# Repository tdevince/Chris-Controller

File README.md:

# Chris-Controller

[](https://private-user-images.githubusercontent.com/97317875/435509045-00b4797d-aa02-43c4-9b9c-edfc26d2068e.mp4?jwt=eyJhbGciOiJIUzI1NiIsInR5cCI6IkpXVCJ9.eyJpc3MiOiJnaXRodWIuY29tIiwiYXVkIjoicmF3LmdpdGh1YnVzZXJjb250ZW50LmNvbSIsImtleSI6ImtleTUiLCJleHAiOjE3NDUxOTc4OTksIm5iZiI6MTc0NTE5NzU5OSwicGF0aCI6Ii85NzMxNzg3NS80MzU1MDkwNDUtMDBiNDc5N2QtYWEwMi00M2M0LTliOWMtZWRmYzI2ZDIwNjhlLm1wND9YLUFtei1BbGdvcml0aG09QVdTNC1ITUFDLVNIQTI1NiZYLUFtei1DcmVkZW50aWFsPUFLSUFWQ09EWUxTQTUzUFFLNFpBJTJGMjAyNTA0MjElMkZ1cy1lYXN0LTElMkZzMyUyRmF3czRfcmVxdWVzdCZYLUFtei1EYXRlPTIwMjUwNDIxVDAxMDYzOVomWC1BbXotRXhwaXJlcz0zMDAmWC1BbXotU2lnbmF0dXJlPWJmYWJlMGNhM2JmNDQzZDk5YWMxNTI0YjNhZTNlNTE5ZTFhZDBlNDViOGY3ZTc2ZDY3YzNkNTc0ZjY5ZTM0MTQmWC1BbXotU2lnbmVkSGVhZGVycz1ob3N0In0.5TFY-foABcXsPSkUT4TwTE6B_hcxhnk4HnvymQrl-RE)

This project is dedicated to my sister who is forced to live with a stationary oxygen concentrator 
in her house. The unit is extremely loud and not placed in a part of the house she wants to sleep 
or be in.  However, to change the oxygen flowrate, it is necessary for someone to do it at the machine.
For someone who is not mobile, this is a dificult task.  Further complicated by the fact that
in order to get up, she must first increase her oxygen flowrate.  Not possible without a caretaker
to go to the unit and manually change it.  

While some oxygen concentrators are available with remote control flow systems, they are not
FDA approved (as of this writing), as such medical supply companies do not provide these
units.

Her options are to increase the flow at the concentrator and use a second flowmeter at her location
that moves with her.  This creates a few problems, first the backpressure for the remote flowmeter
does not allow humidification at the concentrator to work properly.  Thus she is left with dry oxygen
which results in discomfort and nose bleeds.  Second, the backpressure can cause the concetrator
to alarm repeately.  Finally, this requires more hoses at her end of the system, which tangle and 
get caught when she tries to go to her walker or wheel chair.

The following paper by Duke University (https://pmc.ncbi.nlm.nih.gov/articles/PMC10122499/) provides
the basis for which this project is undertaken.  The project recommends that the controller at the 
stationary concentrator communicate via Bluetooth to a iPhone.  This requires an app on the iPhone to
controll the unit at the concentrator.  Since I'm not that well versed in creating applications for
the Apple Store, I instead created a remote control unit (based upon the ESP32-S2 chip, using the
ESP-NOW protocol).  This system uses the 2.4GHz WiFi frequency, but does not require connection
to a local WiFi network.

Since the paper that describes the hardware is a non-commercial license (CC BY-NC 3.0), the hardware
portion of this project is non-commercial. However, the software code developed for this project
is licensed under GNU General Pulbic License

## Repository Files:

* Files necessary for 3D printing are in the folder "3D Print Files".
* The Fusion360 files used to create these files are in the folder titled "Fusion360"
* An instruction manual that describes the operation and use of the system is included as a *.pdf file in the "Instruciton Manual" folder.  
* The circuit was designed using KiCad 9.0.  The schematic as well as the PCB files are in the folder "KiCad 9.0 fiies".  This folder also has the gerber files, position files and BOM files necessary for ordering the PCB's from JLCPCB.com.
* Two other repositories are used for the code used to program the controller and the remote.  The links to these repositories are in the folders "Controller" and "Remote".

## Building the Controller:

To build the Chris Controller, you will need to make the controller as well as the remote control.  The Controller consists of 3 3D printed gears, a mounting plate for the stepper motor and potentiometer and a base and cover.  The Fusion 360 files used to create the files for printing are included.  The parts were output to *stl files that were imported into PrusaSlicer.  The 3D input and output files are included in the Controller Directory.  PETG was used to print all parts. The potentiometer mounting plate requires supports on the dished part that holds the potentiometer.  The Cover has supports on the portion of the opening that accepts the 12V plug.  No other parts required supports for printing.
The stepper motor used is the 28BYJ-48 stepper motor.  This motor is found in 12V and 5V versions.  This project used the 12V version.  The potentiometer uses is the Bourns 3590-2-103L 10k ohm multiturn potentiometer.  The output jack supplied with the stepper motor is the JST 5 pin XH series connector.  The mating male connector is used on the PCB.  The potentiometer is connected to the PCB using the 2 pin JST connectors (XH series as well).  
The controller for the stepper is the ULN2003A Darlington array DIP.  Rather than use an SMT part, the DIP package was used since this is a common failure point of stepper motor systems.  Thus, using a 16pin socket on the PCB, the ULN2003A is easily replaceable.
The PCB uses an ESP32-S2-Solo-2 module for a microcontroller.  This module has the WiFi antenna included.  The code for the controller and remote uses the ESP-NOW protocol for communication.  This eliminates the need for a WiFi connection but provides superior range over a Bluetooth connection.  

The schematic and gerber files to order the PCB are provided in the KiCad directory.  The BOM used to order the PCB’s do not include the ESP32 module or any through hole parts (sockets, etc.) since these are easily added.  The ESP32 module is relatively inexpensive, but when supplied as a separate module, and not part of development kit, it must first be programmed prior to soldering to the PCB.  There is no way to update the firmware of the ESP32 once installed, other than Over-The -Air updates.  Therefore, the first loading of the firmware requires a wired connection to a PC.  Using a development board with flexipins allows for easy programming of the ESP32 module before installing.  If such a board is not available (I made my own for such purposes), the schematic and PCB can be redesigned to use a ESP32-S2-DevkitC-1.  This will increase the footprint of the PCB, but can be made functional.
The power supply used is a standard 12VDC adapter.  The stepper and ULN2003A take 12V inputs, the ESP32 is supplied with 3.3V from a buck switching regulator.  A switching regulator was chosen for its efficiency.  If a linear regulator is used, accommodation for heat dissipation must be considered since dropping from 12V to 3.3V will involve significant heat on linear regulators.

## Building the Remote:

The remote 3d files print a total of 7 items.  These are:
	Remote Cover
	Remote Base
	Up Button
	Down Button
	Battery Box
	Battery Box Cover

The Remote Cover and the Battery Box print as two items each if you want to print text(on the cover) and battery icons (on the battery box).  The text and icons are two different parts in the Fusion360 files.

To print different colors on the same layer in Prusaslicer, first go to “General” settings and change the number of extruders to 2.  Then on the Custom Code, enter “M600” for tool change.  This will cause the printer to pause and prompt to load a new color.  This method works well when only one or two layers need a different color inserted (such as text or battery icons).  When using this method, it is best if the text/icon part is part #2.  This way the rest of the layer is printed first, and success rate is higher in getting the text to look good without lifting or other print errors.

The *.gcode files are set up to print the multicolor as described above.  The cover is designed to have a 1mm thick acrylic sheet as a display window to protect the OLED screen.  The window cover should be cut and fit to the space in the cover before gluing.  Use a 5 minute epoxy rather than a CynoAcrylic (CA, Superglue, etc.) type of glue.  The CA glues will tend to fog the acrylic sheet.

The battery box uses a total of 8 keystone style 5209 terminal clips.  The clips are inserted into the box, and the tabs then bent outward 90 degrees.  The tabs then may be soldered to provide the 4 cells in series (i.e. positive to negative with the first and last tabs being the +6V and -0V tabs).

The positive tab is then routed to the slide switch (the cover is designed to use the CW Industries model G-107-SI-0005 slide switch.  The output of the slide switch, with the negative terminal of the battery box are then connected to the PCB using a JST XH series two pin connector.

Once the battery box is soldered, it may then be glued into the cover.  There are indexing tabs designed into the battery cover for the battery box.  

The two buttons (Up and Down) are also printed in PETG, I used red to offset it from the urban grey I used for the remainder of the remote.  These buttons merely fit inside the cover and are held into position by the PCB and push buttons.  The push buttons used are similar to https://www.amazon.com/Tactile-Switch-Momentary-Arduino-6x6x5mm/dp/B06XRH6GNX

Only two buttons are exposed by to the push buttons that are printed (the up and down buttons).  The calibration button is accessible using a paper clip through the small hole in the upper left of the remote cover.  The fourth button of the PCB is for OTA updates and is not accessible with the cover in place.

The remote uses a 1.3” OLED monochrome I2C display.  Note the order of the 4 contacts on the PCB to ensure that the one you are using will work, if not a redesign of the PCB may be necessary so that SDL, SCL, VCC and GND align.  The OLED uses the SH1106 chip, thus the library for the remote codes is built around this display.

Similar to the controller, the remote uses an ESP32-S2-Solo-2 bare module (https://www.digikey.com/en/products/detail/espressif-systems/ESP32-S2-SOLO-2-N4/16591892?gclid=1df37c397d151f5e88d9143c09d1c049&gclsrc=3p.ds&&utm_adgroup=General&utm_source=bing&utm_medium=cpc&utm_campaign=Dynamic%20Search_EN_RLSA_Cart&utm_term=digikey&utm_content=General&utm_id=bi_cmp-384476623_adg-1302921504343591_ad-81432677981980_dat-2333232393680003:loc-190_dev-c_ext-_prd-&msclkid=1df37c397d151f5e88d9143c09d1c049) .  

The module will need to be programmed before soldering to the PCB, so that OTA updates are possible.  The advantage of using the bare module rather than development board is that it drastically reduces the footprint on the PCB (thus a smaller remote) as well as reducing the vampire load when the module is put to sleep.  Most development boards use a linear voltage regulator, which will consume much more battery power than the switching regulator used in this design.

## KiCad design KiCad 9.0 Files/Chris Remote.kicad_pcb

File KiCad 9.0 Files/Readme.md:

This folder contains the KiCad files for the schematic and PCB layout
in the formate required by JLCPCB.com.  Also included is the BOM and
position file that JLCPCB requires for assembly.  The BOM and postion
file do not include information the push buttons, connectors or
ESP32-S2-Solo-2 module since these are manually soldered after
receipt of the manufactured PCB's.

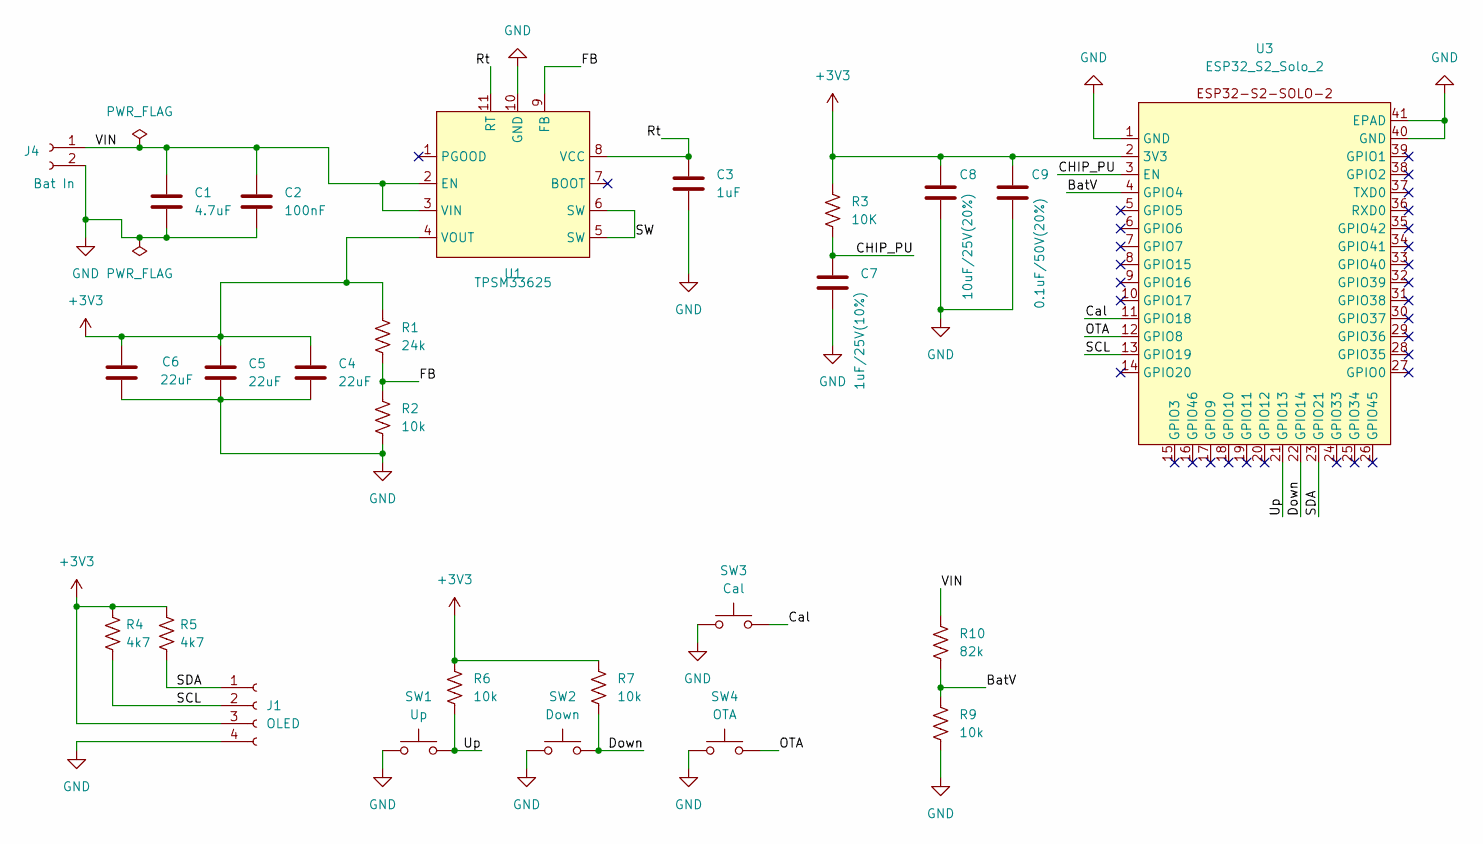
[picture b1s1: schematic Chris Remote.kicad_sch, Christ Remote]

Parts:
C1: 4.7uF; C_1206_3216Metric; LCSC Part Number C29823
C2: 100nF; C_0402_1005Metric; LCSC Part Number C307331
C3: 1uF; C_1206_3216Metric; LCSC Part Number C1848
C4, C5, C6: 22uF; C_0805_2012Metric; LCSC Part Number C45783
C7: 1uF/25V(10%); C_0402_1005Metric; LCSC Part Number C52923
C8: 10uF/25V(20%); C_0603_1608Metric; LCSC Part Number C96446
C9: 0.1uF/50V(20%); C_0603_1608Metric; LCSC Part Number C14663
J1: OLED; PinHeader_1x04_P2.54mm_Vertical
J4: Bat In; JST_XH_B2B-XH-A_1x02_P2.50mm_Vertical
R1: 24k; R_0603_1608Metric; LCSC Part Number C23352
R2, R6, R7, R9: 10k; R_0603_1608Metric; LCSC Part Number C25804
R3: 10K; R_0402_1005Metric; LCSC Part Number C25744
R4, R5: 4k7; R_0603_1608Metric; LCSC Part Number C23162
R10: 82k; R_0603_1608Metric; LCSC Part Number C23254
SW1: Up; SW_PUSH_6mm_H5mm
SW2: Down; SW_PUSH_6mm_H5mm
SW3: Cal; SW_PUSH_6mm_H5mm
SW4: OTA; SW_PUSH_6mm_H5mm
U1: TPSM33625; QFN-FCMOD; LCSC Part Number C7073593
U3: ESP32_S2_Solo_2; ESP32_S2_SOLO_2

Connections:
+3V3: C4.1, C5.1, C6.1, C8.1, C9.1, J1.3, R1.1, R3.1, R4.1, R5.1, R6.1, R7.1, U1.4 (VOUT), U3.2 (3V3)
/BatV: R9.1, R10.2, U3.4 (GPIO4)
/CHIP_PU: C7.1, R3.2, U3.3 (EN)
/Cal: SW3.2, U3.11 (GPIO18)
/Down: R7.2, SW2.2, U3.22 (GPIO14)
/FB: R1.2, R2.1, U1.9 (FB)
/OTA: SW4.2, U3.12 (GPIO8)
/Rt: C3.1, U1.8 (VCC), U1.11 (RT)
/SCL: J1.2, R4.2, U3.13 (GPIO19)
/SDA: J1.1, R5.2, U3.23 (GPIO21)
/SW: U1.5 (SW), U1.6 (SW)
/Up: R6.2, SW1.2, U3.21 (GPIO13)
/VIN: C1.1, C2.1, J4.1, R10.1, U1.2 (EN), U1.3 (VIN)
GND: C1.2, C2.2, C3.2, C4.2, C5.2, C6.2, C7.2, C8.2, C9.2, J1.4, J4.2, R2.2, R9.2, SW1.1, SW2.1, SW3.1, SW4.1, U1.10 (GND), U3.1 (GND), U3.40 (GND), U3.41 (EPAD)

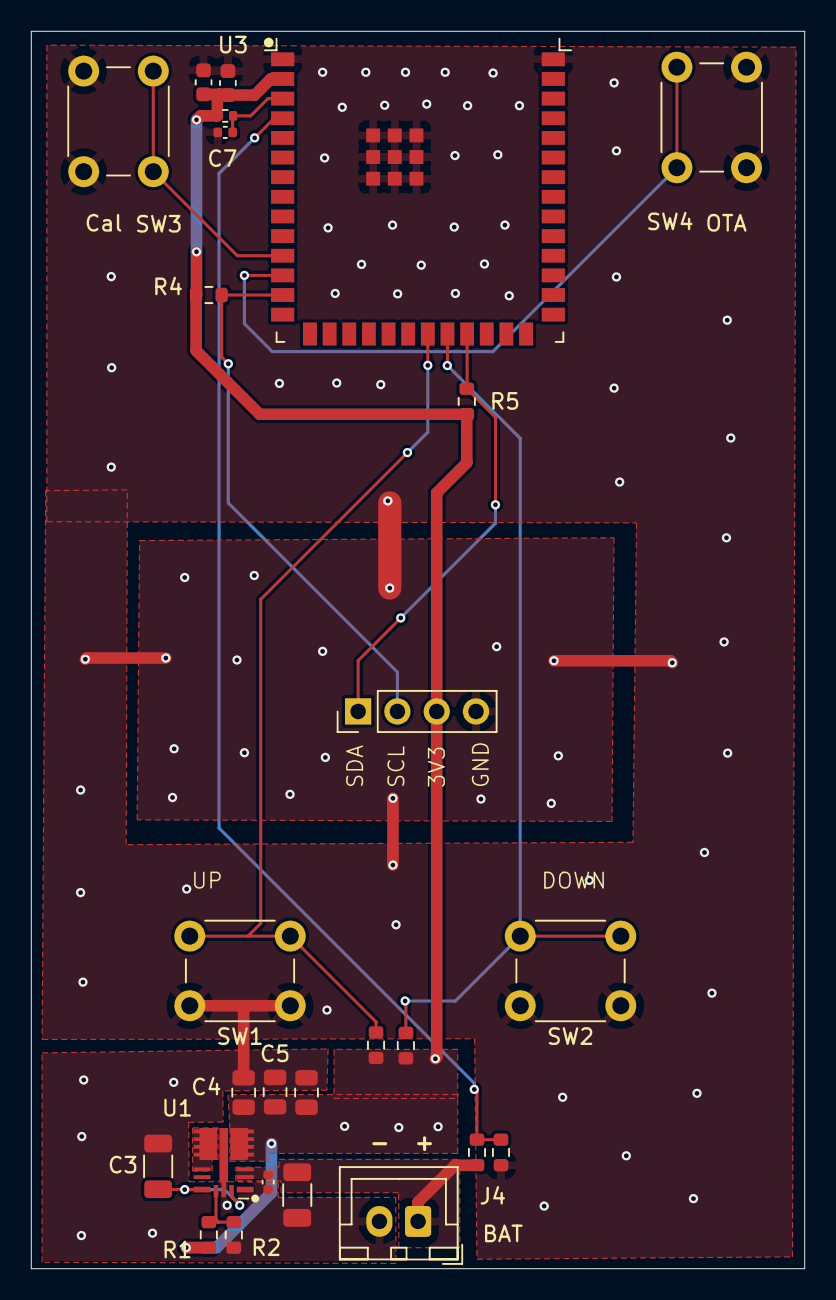
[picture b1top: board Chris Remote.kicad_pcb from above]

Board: 2 copper layers, 50.0 x 80.0 mm, 26 parts (0 on the bottom side), 14 nets.

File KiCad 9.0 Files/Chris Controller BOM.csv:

Comment,Designator,Footprint,LCSC Part Number
4.7uF,C1,Capacitor_SMD:C_1206_3216Metric,C29823
100nF,C2,Capacitor_SMD:C_0402_1005Metric,C307331
1uF,C3,Capacitor_SMD:C_1206_3216Metric,C1848
22uF,"C4,C5,C6",Capacitor_SMD:C_0805_2012Metric,C45783
1uF/25V(10%),C7,Capacitor_SMD:C_0402_1005Metric,C52923
10uF/25V(20%),C8,Capacitor_SMD:C_0603_1608Metric,C96446
0.1uF/50V(20%),C9,Capacitor_SMD:C_0603_1608Metric,C14663
24k,R1,Resistor_SMD:R_0603_1608Metric,C23352
10k,R2,Resistor_SMD:R_0603_1608Metric,C25804
10K,R3,Resistor_SMD:R_0402_1005Metric,C25744
22k,R4,Resistor_SMD:R_0603_1608Metric,C31850
TPSM33625,U1,Library:QFN-FCMOD,C7073593

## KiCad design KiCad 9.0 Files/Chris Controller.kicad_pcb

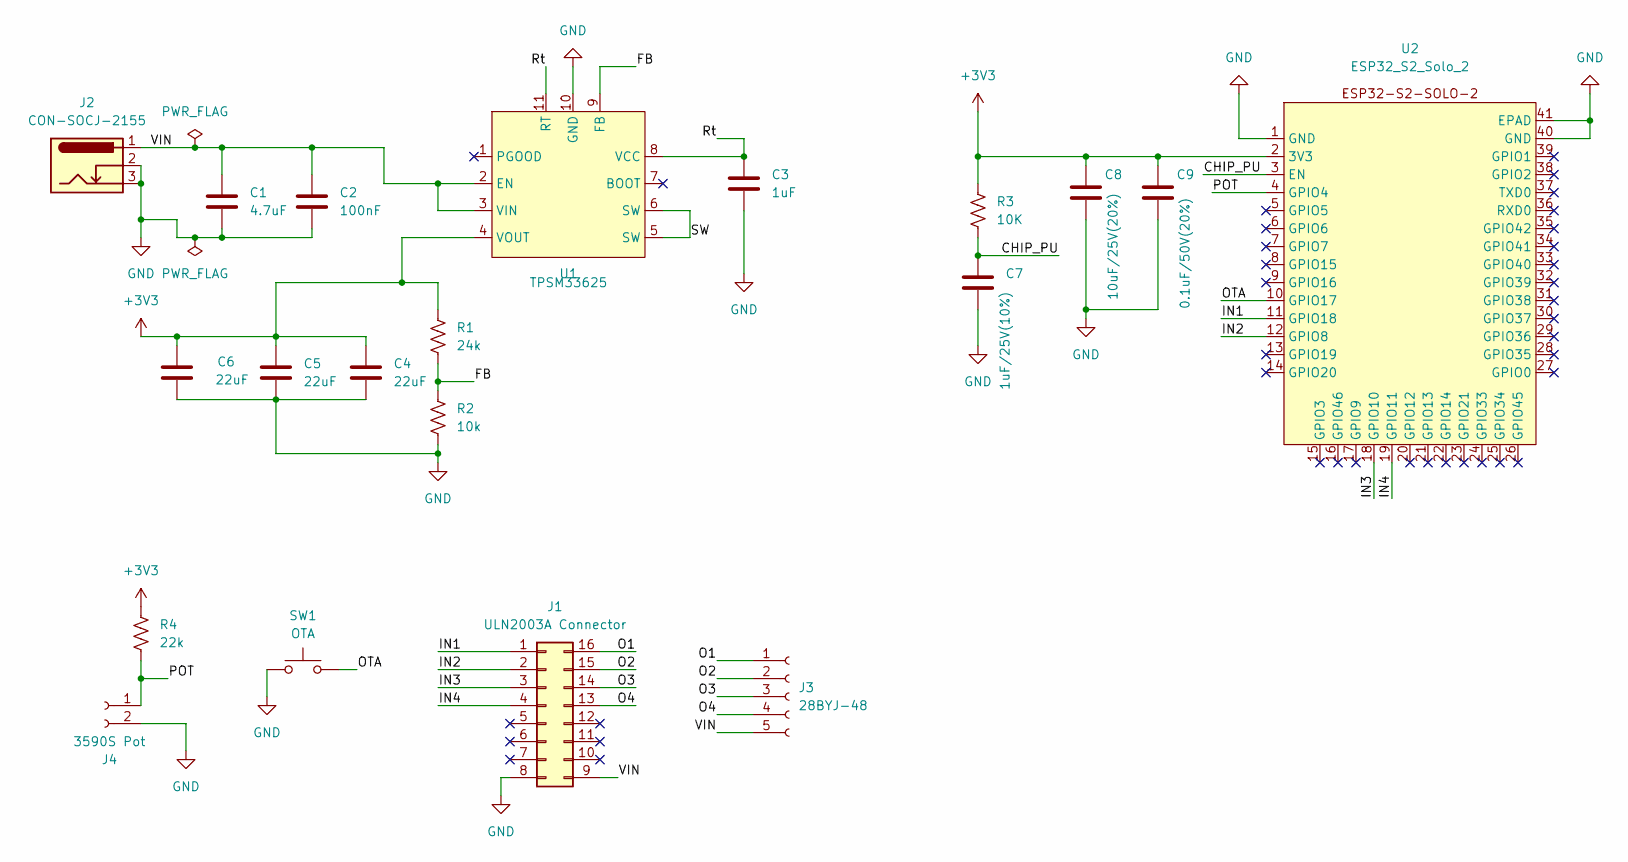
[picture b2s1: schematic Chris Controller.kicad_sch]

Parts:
C1: 4.7uF; C_1206_3216Metric; LCSC Part Number C29823
C2: 100nF; C_0402_1005Metric; LCSC Part Number C307331
C3: 1uF; C_1206_3216Metric; LCSC Part Number C1848
C4, C5, C6: 22uF; C_0805_2012Metric; LCSC Part Number C45783
C7: 1uF/25V(10%); C_0402_1005Metric; LCSC Part Number C52923
C8: 10uF/25V(20%); C_0603_1608Metric; LCSC Part Number C96446
C9: 0.1uF/50V(20%); C_0603_1608Metric; LCSC Part Number C14663
J1: ULN2003A Connector; DIP-16_W7.62mm_Socket
J2: CON-SOCJ-2155; GRAVITECH_CON-SOCJ-2155
J3: 28BYJ-48; JST_XH_B5B-XH-A_1x05_P2.50mm_Vertical
J4: 3590S Pot; JST_XH_B2B-XH-A_1x02_P2.50mm_Vertical
R1: 24k; R_0603_1608Metric; LCSC Part Number C23352
R2: 10k; R_0603_1608Metric; LCSC Part Number C25804
R3: 10K; R_0402_1005Metric; LCSC Part Number C25744
R4: 22k; R_0603_1608Metric; LCSC Part Number C31850
SW1: OTA; SW_PUSH_6mm_H5mm
U1: TPSM33625; QFN-FCMOD; LCSC Part Number C7073593
U2: ESP32_S2_Solo_2; ESP32_S2_SOLO_2

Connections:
+3V3: C4.1, C5.1, C6.1, C8.1, C9.1, R1.1, R3.1, R4.1, U1.4 (VOUT), U2.2 (3V3)
/CHIP_PU: C7.1, R3.2, U2.3 (EN)
/FB: R1.2, R2.1, U1.9 (FB)
/IN1: J1.1, U2.11 (GPIO18)
/IN2: J1.2, U2.12 (GPIO8)
/IN3: J1.3, U2.18 (GPIO10)
/IN4: J1.4, U2.19 (GPIO11)
/O1: J1.16, J3.1
/O2: J1.15, J3.2
/O3: J1.14, J3.3
/O4: J1.13, J3.4
/OTA: SW1.2, U2.10 (GPIO17)
/POT: J4.1, R4.2, U2.4 (GPIO4)
/Rt: C3.1, U1.8 (VCC), U1.11 (RT)
/SW: U1.5 (SW), U1.6 (SW)
/VIN: C1.1, C2.1, J1.9, J2.1, J3.5, U1.2 (EN), U1.3 (VIN)
GND: C1.2, C2.2, C3.2, C4.2, C5.2, C6.2, C7.2, C8.2, C9.2, J1.8, J2.2, J2.3, J4.2, R2.2, SW1.1, U1.10 (GND), U2.1 (GND), U2.40 (GND), U2.41 (EPAD)

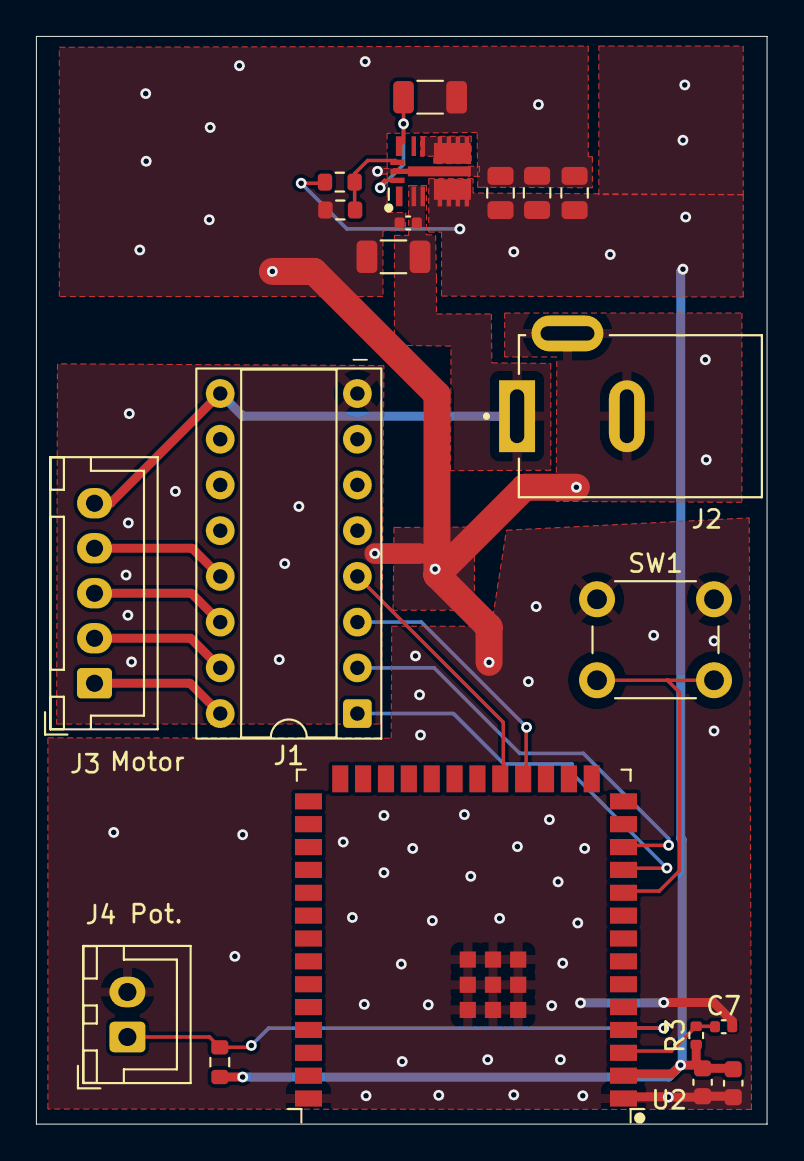
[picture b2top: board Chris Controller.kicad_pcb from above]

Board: 2 copper layers, 40.6 x 60.4 mm, 20 parts (0 on the bottom side), 17 nets.

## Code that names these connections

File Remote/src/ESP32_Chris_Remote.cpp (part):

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#define UpButton              GPIO_NUM_13     // Only RTC IO are allowed for Wake - ESP32 Pin example
#define DownButton              GPIO_NUM_14     // Only RTC IO are allowed for Wake - ESP32 Pin example
#define CalButton              GPIO_NUM_18     // Calibration of the Controller
#define OTAButton              GPIO_NUM_8     // OTA update 
#define BattPin                GPIO_NUM_4     //ADC measurement of Battery voltage
#define I2C_ADDRESS 0x3C // I2C address for the OLED display
#define I2C_SDA 21 // SDA pin for ESP32
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volatile bool updateOTA=false; // Flag to check if OTA update is needed
volatile bool CalMode=false;
volatile int8_t rssiVal;
uint32_t LastOTAPress=0; // Last time the OTA button was pressed
uint32_t PressInterval=500; // Interval to check for OTA button press
uint32_t LastCalPress=0; // Last time the Cal button was pressed
uint32_t LastDemandTime=0;// Last time up or down flow button pressed
bool UpButtonPressed=false;
bool DownButtonPressed=false;
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  // Check if the interval has passed
  if (millis() - previousMillis >= interval) {
    previousMillis = millis(); // Save the last update time
    // Read the state of GPIO13 and GPIO14
    bool upState = digitalRead(UpButton) == LOW; // LOW means pressed
    bool downState = digitalRead(DownButton) == LOW; // LOW means pressed

    // Update O2Flow based on the states of GPIO13 and GPIO14
    if (upState && !downState) {//Up button pressed
      DemandButtonPressed=true;
      O2Flow += 0.5; // Increment O2Flow if GPIO13 is low and GPIO14 is high
      if(O2Flow>10.0) O2Flow=10.0; //limit max flow to 10.0 L/min
      LastDemandTime=millis();
      LastIdleTime=millis();
    } else if (!upState && downState) {//down button pressed
      DemandButtonPressed=true;
      O2Flow -= 0.5; // Decrement O2Flow if GPIO14 is low and GPIO13 is high
      if(O2Flow<2.0) O2Flow=2.0; //limit min flow to 2.0 L/min
      LastDemandTime=millis();
      LastIdleTime=millis();
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
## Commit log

2025-03-28 Create Readme.md
    KiCad 9.0 files giving schematics, PCB layout, LSCS Part numbers which are necessary to have JLCPCB.com manufacture the PCB's
2025-03-28 Update LICENSE
2025-03-28 Update LICENSE
    use GNU General Public license for software
    use CC BY-NC-4.0 non-commercial license for hardware
2025-04-13 Create Remote
2025-04-15 Update Readme
    Redirect to ESP32_Chris_Controller repository for code
2025-04-15 Update Readme
    editorial changes
2025-04-15 Update Readme
    Redirect to ESP32_Chris_Remote repository for code
2025-04-17 Update README.md
    Added notes on construction of the controller
2025-04-20 Update README.md
    Added description for building the remote
2025-04-20 Update README.md
    Add list of folders and descriptions
2025-04-20 Update README.md
    Add formatting
2025-04-20 Update README.md
    formatting changes
2025-04-20 Update README.md
    Added video
2025-04-20 Update README.md
    update media file link
